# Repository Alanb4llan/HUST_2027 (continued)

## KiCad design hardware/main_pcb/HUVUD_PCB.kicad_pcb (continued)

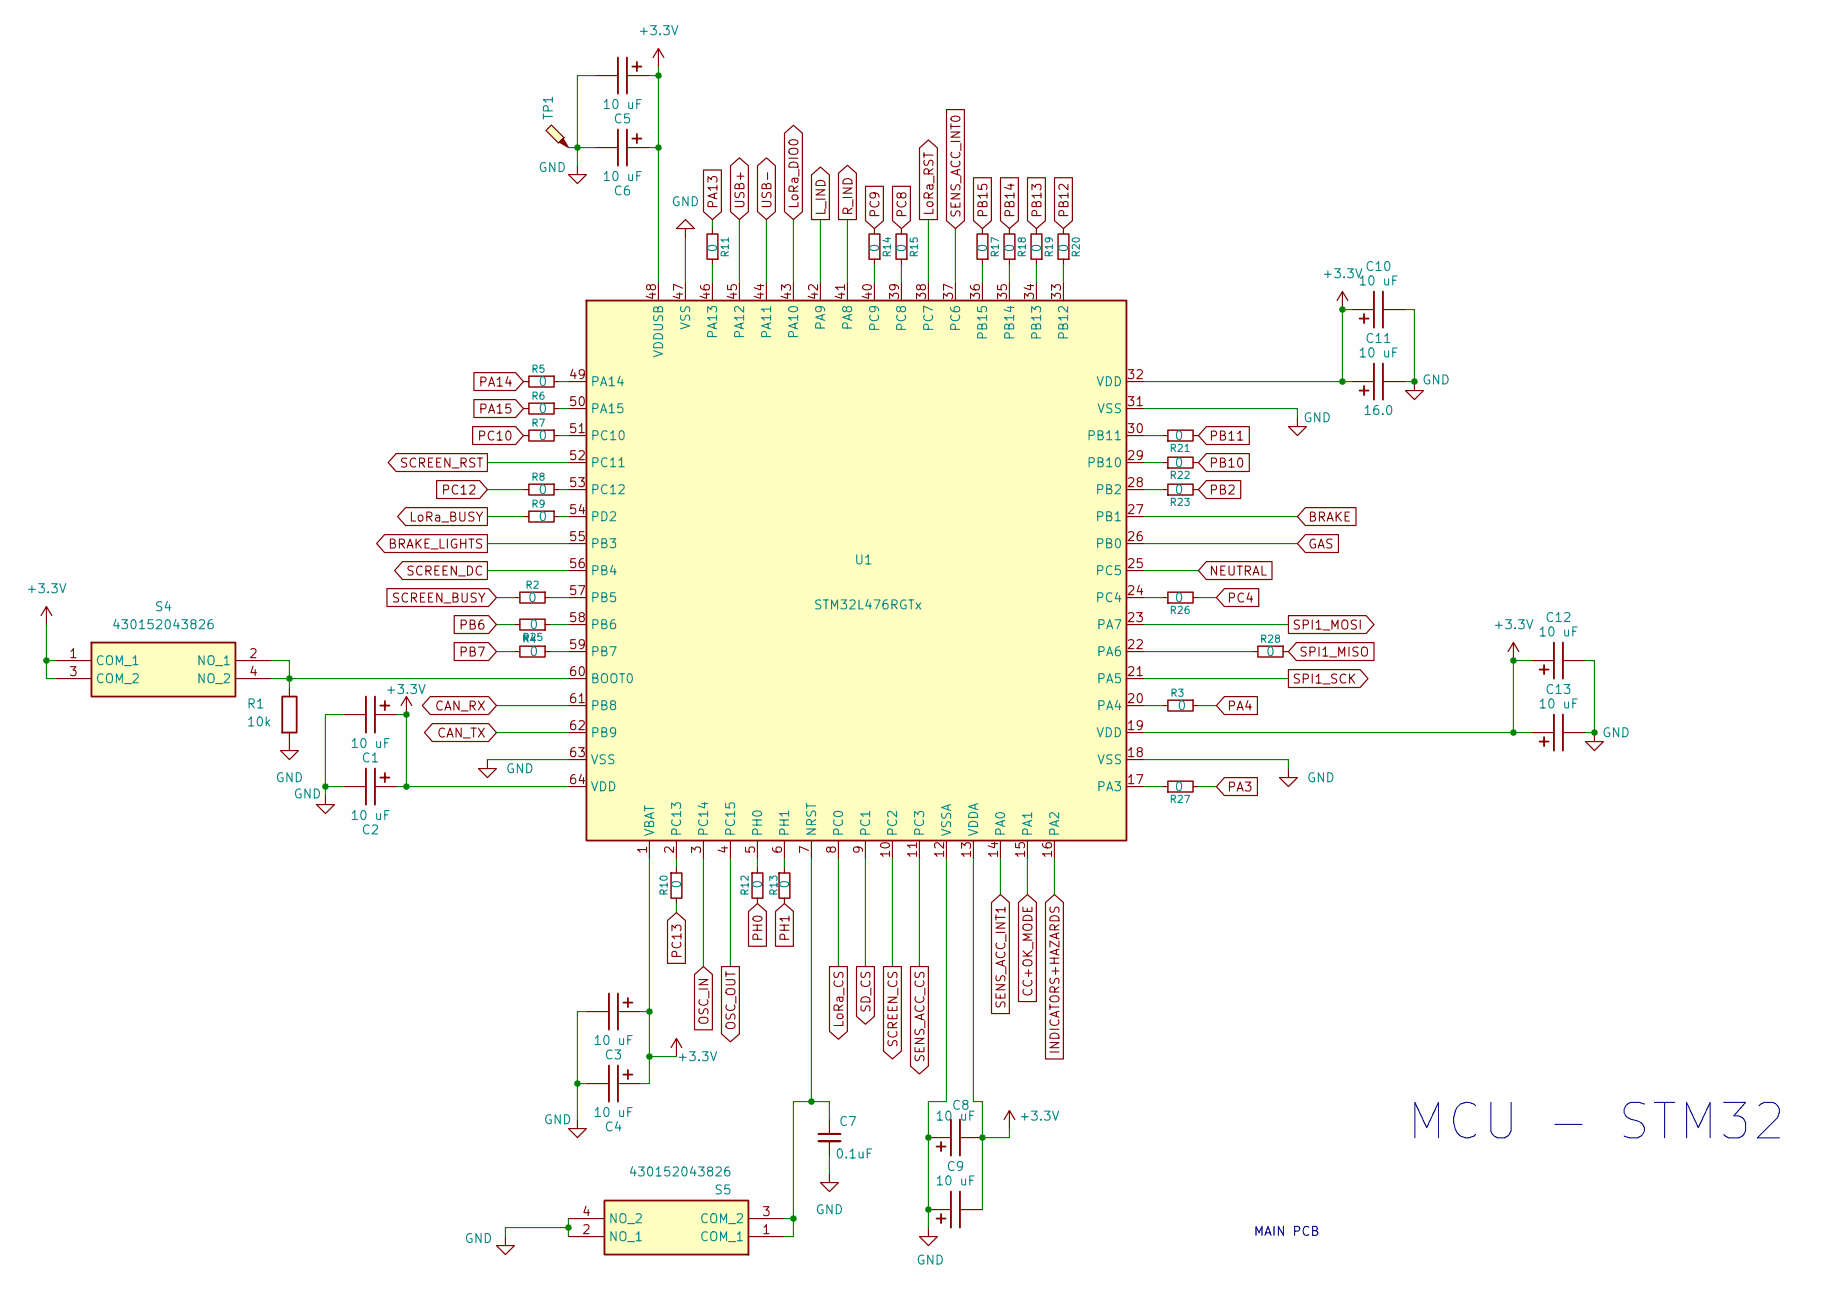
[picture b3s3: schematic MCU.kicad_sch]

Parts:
C1, C2, C3, C4, C5, C6, C8, C9, C10, C11, C12, C13: 10 uF; C_0603_1608Metric_Pad1.08x0.95mm_HandSolder; Voltage 16.0; Part Number 865080340001
C7: 0.1uF; C_0603_1608Metric_Pad1.08x0.95mm_HandSolder
R1: 10k; R_Wurth_WRIS-RSKS-0603_W
R2, R3, R4, R5, R6, R7, R8, R9, R10, R11, R12, R13, R14, R15, R17, R18, R19, R20, R21, R22, R23, R25, R26, R27, R28: 0; R_Wurth_WRIS-RSKS-0603_W
S4, S5: 430152043826; SW_Wurth_WS-TASV_430152043826; Mouser Part Number 710-430152043826
TP1: TestPoint_Probe; TestPoint_THTPad_2.0x2.0mm_Drill1.0mm
U1: STM32L476RGTx; LQFP-64_10x10mm_P0.5mm

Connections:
+3.3V: C1.1, C2.1, C3.1, C4.1, C5.1, C6.1, C8.2, C9.2, C10.1, C11.1, C12.1, C13.1, S4.1 (COM_1), S4.3 (COM_2), U1.1 (VBAT), U1.13 (VDDA), U1.19 (VDD), U1.32 (VDD), U1.48 (VDDUSB), U1.64 (VDD); also elsewhere on the board
BRAKE: U1.27 (PB1); also elsewhere on the board
BRAKE_LIGHTS: U1.55 (PB3); also elsewhere on the board
CAN_RX: U1.61 (PB8); also elsewhere on the board
CAN_TX: U1.62 (PB9); also elsewhere on the board
CC+OK_MODE: U1.15 (PA1); also elsewhere on the board
GAS: U1.26 (PB0); also elsewhere on the board
GND: C1.2, C2.2, C3.2, C4.2, C5.2, C6.2, C7.2, C8.1, C9.1, C10.2, C11.2, C12.2, C13.2, R1.2, S5.2 (NO_1), S5.4 (NO_2), TP1.1, U1.12 (VSSA), U1.18 (VSS), U1.31 (VSS), U1.47 (VSS), U1.63 (VSS); also elsewhere on the board
INDICATORS+HAZARDS: U1.16 (PA2); also elsewhere on the board
L_IND: U1.42 (PA9); also elsewhere on the board
LoRa_BUSY: R9.2; also elsewhere on the board
LoRa_CS: U1.8 (PC0); also elsewhere on the board
LoRa_DIO0: U1.43 (PA10); also elsewhere on the board
LoRa_RST: U1.38 (PC7); also elsewhere on the board
NEUTRAL: U1.25 (PC5); also elsewhere on the board
unnamed: R1.1, S4.2 (NO_1), S4.4 (NO_2), U1.60 (BOOT0)
unnamed: C7.1, S5.1 (COM_1), S5.3 (COM_2), U1.7 (NRST)
unnamed: R27.1, U1.17 (PA3)
unnamed: R3.2, U1.20 (PA4)
unnamed: R28.2, U1.22 (PA6)
unnamed: R11.1, U1.46 (PA13)
unnamed: R5.1, U1.49 (PA14)
unnamed: R6.1, U1.50 (PA15)
unnamed: R23.1, U1.28 (PB2)
unnamed: R2.1, U1.57 (PB5)
unnamed: R25.1, U1.58 (PB6)
unnamed: R4.1, U1.59 (PB7)
unnamed: R22.1, U1.29 (PB10)
unnamed: R21.1, U1.30 (PB11)
unnamed: R20.1, U1.33 (PB12)
unnamed: R19.1, U1.34 (PB13)
unnamed: R18.1, U1.35 (PB14)
unnamed: R17.1, U1.36 (PB15)
unnamed: R26.1, U1.24 (PC4)
unnamed: R15.1, U1.39 (PC8)
unnamed: R14.1, U1.40 (PC9)
unnamed: R7.1, U1.51 (PC10)
unnamed: R8.1, U1.53 (PC12)
unnamed: R10.1, U1.2 (PC13)
unnamed: R9.1, U1.54 (PD2)
unnamed: R12.1, U1.5 (PH0)
unnamed: R13.1, U1.6 (PH1)
OSC_IN: U1.3 (PC14); also elsewhere on the board
OSC_OUT: U1.4 (PC15); also elsewhere on the board
PA3: R27.2
PA4: R3.1
PA13: R11.2; also elsewhere on the board
PA14: R5.2; also elsewhere on the board
PA15: R6.2; also elsewhere on the board
PB2: R23.2; also elsewhere on the board
PB6: R25.2; also elsewhere on the board
PB7: R4.2; also elsewhere on the board
PB10: R22.2; also elsewhere on the board
PB11: R21.2; also elsewhere on the board
PB12: R20.2; also elsewhere on the board
PB13: R19.2; also elsewhere on the board
PB14: R18.2; also elsewhere on the board
PB15: R17.2; also elsewhere on the board
PC4: R26.2
PC8: R15.2; also elsewhere on the board
PC9: R14.2; also elsewhere on the board
PC10: R7.2; also elsewhere on the board
PC12: R8.2; also elsewhere on the board
PC13: R10.2; also elsewhere on the board
PH0: R12.2; also elsewhere on the board
PH1: R13.2
R_IND: U1.41 (PA8); also elsewhere on the board
SCREEN_BUSY: R2.2; also elsewhere on the board
SCREEN_CS: U1.10 (PC2); also elsewhere on the board
SCREEN_DC: U1.56 (PB4); also elsewhere on the board
SCREEN_RST: U1.52 (PC11); also elsewhere on the board
SD_CS: U1.9 (PC1); also elsewhere on the board
SENS_ACC_CS: U1.11 (PC3); also elsewhere on the board
SENS_ACC_INT0: U1.37 (PC6); also elsewhere on the board
SENS_ACC_INT1: U1.14 (PA0); also elsewhere on the board
SPI1_MISO: R28.1; also elsewhere on the board
SPI1_MOSI: U1.23 (PA7); also elsewhere on the board
SPI1_SCK: U1.21 (PA5); also elsewhere on the board
USB+: U1.45 (PA12); also elsewhere on the board
USB-: U1.44 (PA11); also elsewhere on the board

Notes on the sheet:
MCU - STM32
MAIN PCB

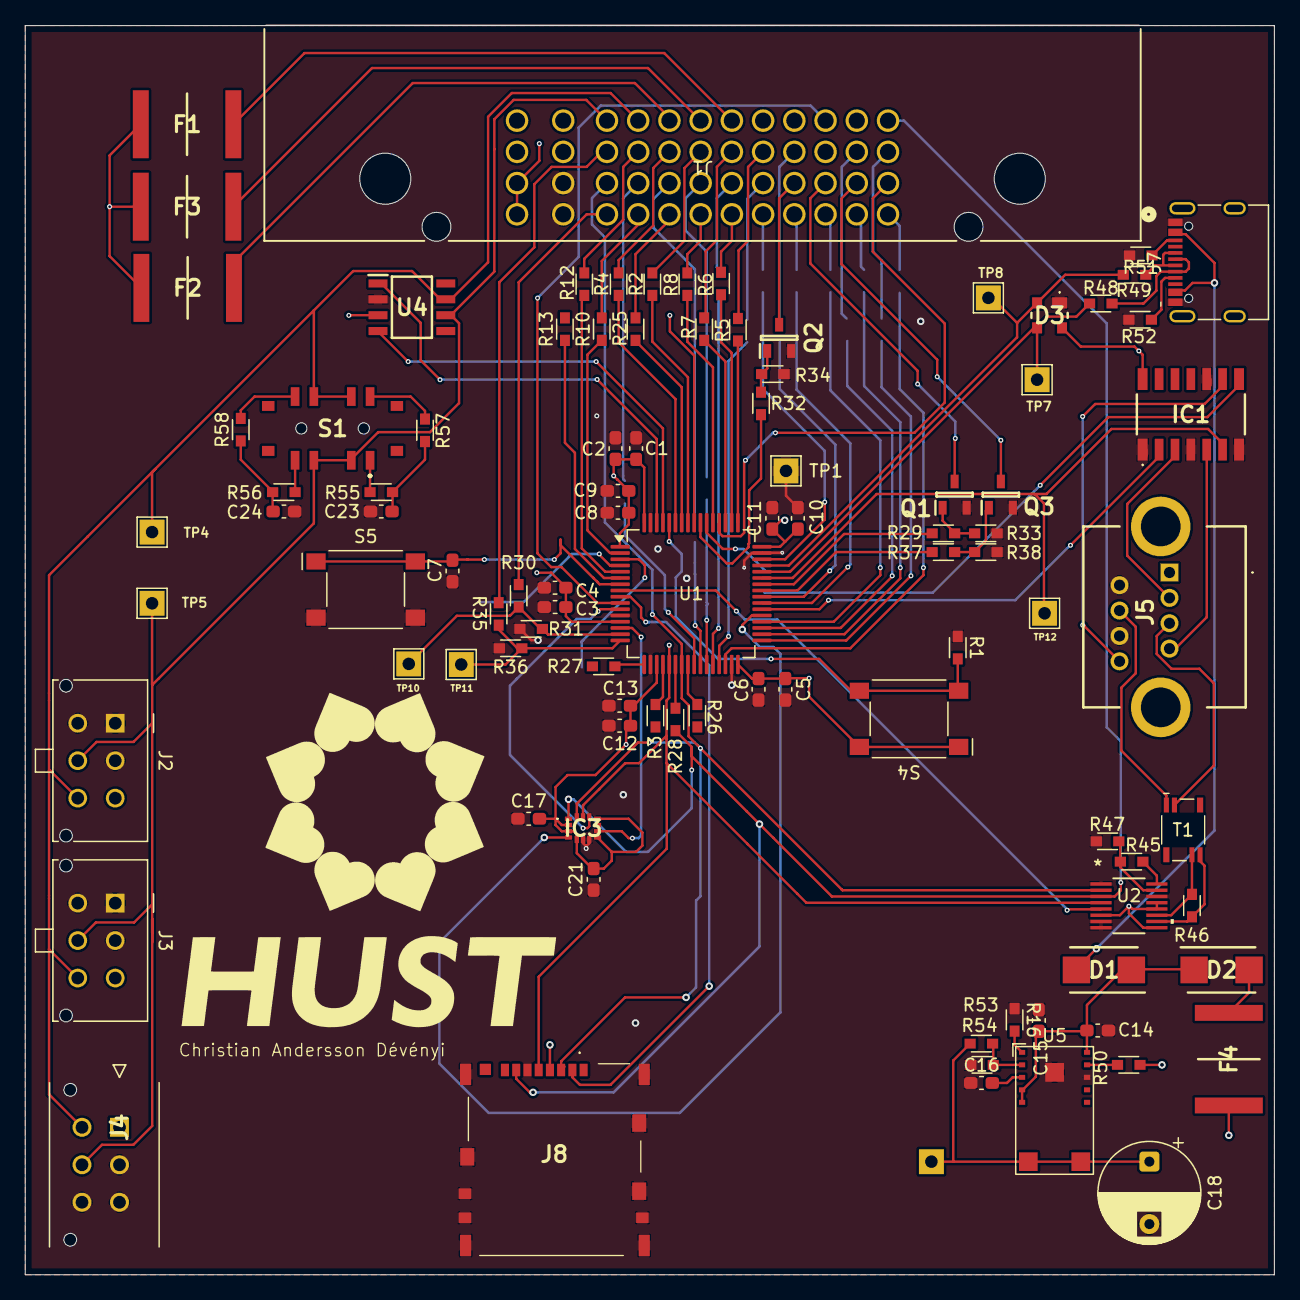
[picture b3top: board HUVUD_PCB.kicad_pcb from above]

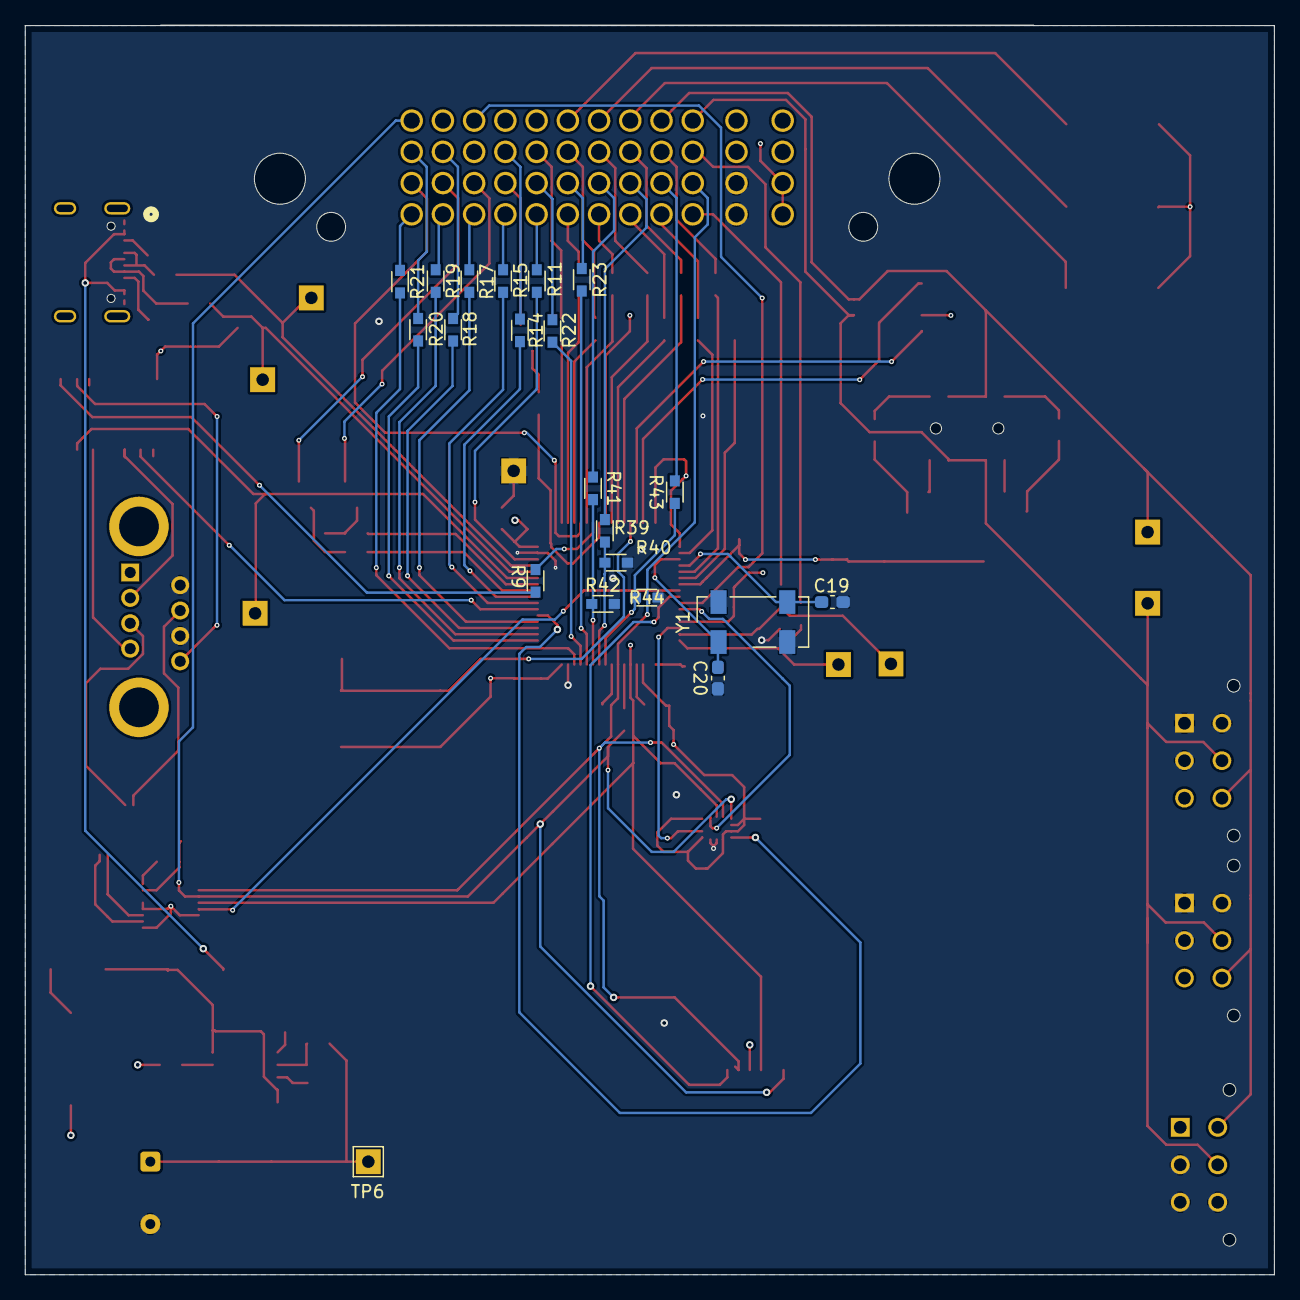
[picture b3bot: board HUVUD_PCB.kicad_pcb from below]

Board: 4 copper layers, 100.0 x 100.0 mm, 117 parts (21 on the bottom side), 120 nets.

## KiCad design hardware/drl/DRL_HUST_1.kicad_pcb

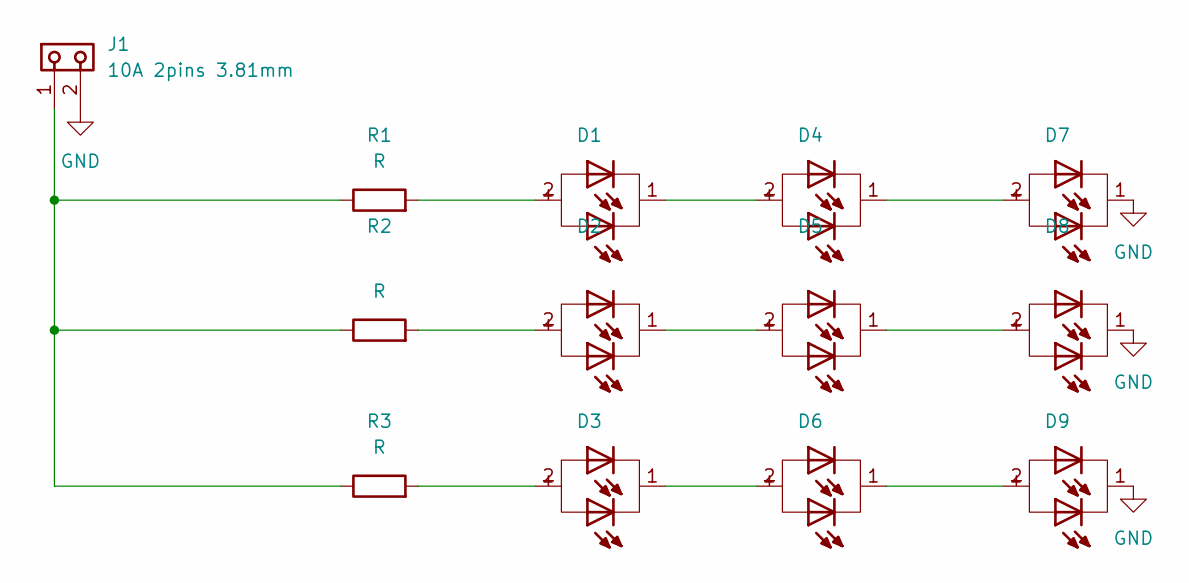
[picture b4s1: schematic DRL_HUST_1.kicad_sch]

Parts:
D1, D2, D3, D4, D5, D6, D7, D8, D9: 3030_158303250A; D_Wurth_WL-SWTP-3030; Part Number 158303250A
J1: 691409320002; J_Wurth_WR-TBL_691409320002; Part Number 691409320002
R1, R2, R3: R; R_0603_1608Metric_Pad0.98x0.95mm_HandSolder

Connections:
GND: D7.1 (-), D8.1 (-), D9.1 (-), J1.2, J1.M2
unnamed: D1.2 (+), R1.2
unnamed: D1.1 (-), D4.2 (+)
unnamed: D2.2 (+), R2.2
unnamed: D2.1 (-), D5.2 (+)
unnamed: D3.2 (+), R3.2
unnamed: D3.1 (-), D6.2 (+)
unnamed: D4.1 (-), D7.2 (+)
unnamed: D5.1 (-), D8.2 (+)
unnamed: D6.1 (-), D9.2 (+)
unnamed: J1.1, J1.M1, R1.1, R2.1, R3.1

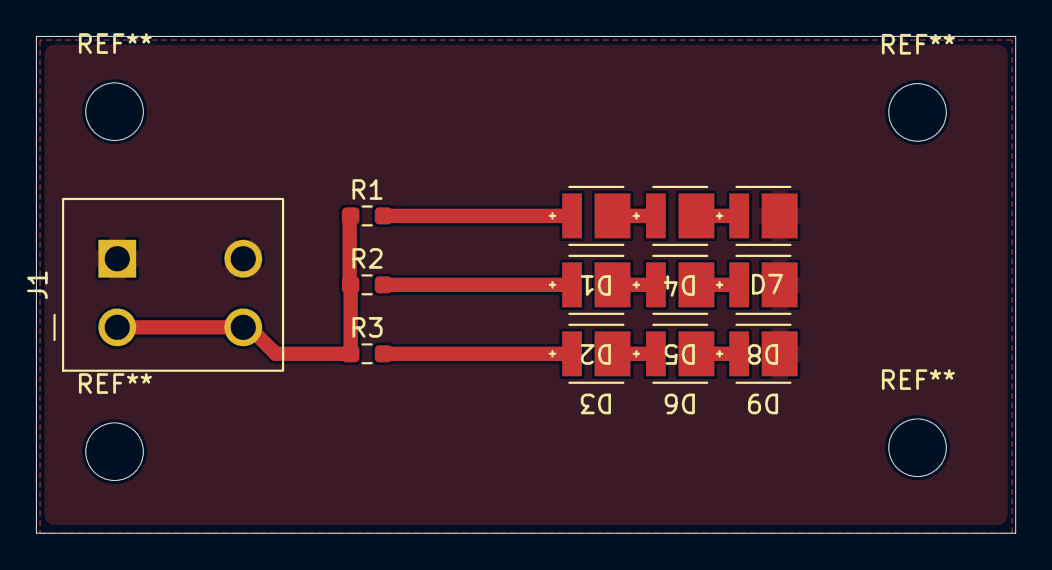
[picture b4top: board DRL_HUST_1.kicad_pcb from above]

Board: 2 copper layers, 54.4 x 27.6 mm, 13 parts (0 on the bottom side), 11 nets.

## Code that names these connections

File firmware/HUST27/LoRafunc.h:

#ifndef LORAFUNC_H
#define LORAFUNC_H

#include <LoRa.h>
#include <SPI.h>
#include <Arduino.h>
#include "global.h"

// Pins for Nucleo-L4R6G + RFM95W
// NSS=D10, SCK=D13, MISO=D12, MOSI=D11, RST=D9, DIO0=D2

#define LORA_SS   PC0   // NSS (Chip Select)
#define LORA_RST  PC7    // Reset
#define LORA_DIO0 PA10    // DIO0 (interrupt)
#define LORA_SCK  PA5
#define LORA_MISO PA6
#define LORA_MOSI PA7

// ==================================================================================
// DATA STRUCTURES FOR EFFICIENT TRANSMISSION
// ==================================================================================

// Structure 1: Critical Vehicle Data (Priority 1)
struct CriticalData {
  float velocity;          // km/h
  float packVoltage;       // V
  float packCurrent;       // A
  float motorCurrent;      // A
  uint8_t flags;           // Bit flags for errors/warnings [0]MCerror [1]BMSerror [2]HighTemp [3]Left [4]Right [5]Hazard [6]CC
  uint16_t counter;        // Packet counter 
} __attribute__((packed));

// Structure 2: Battery Data (Priority 2)
struct BatteryData {
  float lowCellVoltage;    // V
  float highCellVoltage;   // V
  float avgCellVoltage;    // V
  uint8_t cellHighTemp;    // °C
  uint8_t cellLowTemp;     // °C
  uint8_t cellAvgTemp;     // °C
  uint8_t bmsInternalTemp; // °C
  uint16_t counter;        // Packet counter
} __attribute__((packed));

// Structure 3: Motor & Thermal Data (Priority 3)
struct MotorThermalData {
  float motorTemp;         // °C
  float heatSinkTemp;      // °C
  float distance;          // km
  uint16_t counter;        // Packet counter
} __attribute__((packed));

// Structure 4: MPPT Data (Priority 4)
struct MPPTData {
  float mppt1Power;        // W
  float mppt2Power;        // W
  float mppt3Power;        // W
  float totalPower;        // W
  uint16_t counter;        // Packet counter
} __attribute__((packed));


void setupLoRa();
void sendLoRaTestMessage();  
void receiveLoRaMessage(); 
void sendConsolidatedPacket();

#endif

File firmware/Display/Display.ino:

#include <Wire.h>
#include <Adafruit_GFX.h>
#include <Adafruit_SSD1306.h>
#include <DHT.h>

#include "display.h"

// ================= SCREEN =================
#define SCREEN_WIDTH 128
#define SCREEN_HEIGHT 64

Adafruit_SSD1306 display(SCREEN_WIDTH, SCREEN_HEIGHT, &Wire, -1);

// ================= BUTTONS (CHANGE FOR YOUR BOARD) =================
// ⚠️ These are placeholders — uncomment and set correct pins for your STM32
#define BTN_HAZARD PA0
#define BTN_RIGHT  PA1
#define BTN_LEFT   PA2

// ================= DHT (OPTIONAL HARDWARE) =================
#define DHTPIN PA3
#define DHTTYPE DHT11

DHT dht(DHTPIN, DHTTYPE);

// ================= STATES =================
bool hazard = false;
bool leftActive = false;
bool rightActive = false;

bool lastHazardState = HIGH;
bool lastLeftState = HIGH;
bool lastRightState = HIGH;

bool blinkState = false;

// ================= SPEED =================
int speed = 1;

// ================= TIMERS =================
unsigned long lastBlink = 0;
unsigned long lastSpeedUpdate = 0;

// ================= SETUP =================
void setup() {

  Serial.begin(115200);

  // STM32 Wire init (default I2C pins depend on board)
  Wire.begin();

  // Buttons
  pinMode(BTN_HAZARD, INPUT_PULLUP);
  pinMode(BTN_RIGHT, INPUT_PULLUP);
  pinMode(BTN_LEFT, INPUT_PULLUP);

  // DHT (OK even if not used yet)
  dht.begin();

  // OLED init
  if (!display.begin(SSD1306_SWITCHCAPVCC, 0x3C)) {
    while (true); // stop if display fails
  }

  display.clearDisplay();
  display.display();
}

// ================= LOOP =================
void loop() {

  bool hazardBtn = digitalRead(BTN_HAZARD);
  bool rightBtn = digitalRead(BTN_RIGHT);
  bool leftBtn = digitalRead(BTN_LEFT);

  if (hazardBtn == LOW && lastHazardState == HIGH) {
    hazard = !hazard;

    if (hazard) {
      leftActive = false;
      rightActive = false;
    }
  }
  lastHazardState = hazardBtn;

  if (leftBtn == LOW && lastLeftState == HIGH) {
    leftActive = !leftActive;

    if (leftActive) {
      rightActive = false;
      hazard = false;
    }
  }
  lastLeftState = leftBtn;

  if (rightBtn == LOW && lastRightState == HIGH) {
    rightActive = !rightActive;

    if (rightActive) {
      leftActive = false;
      hazard = false;
    }
  }
  lastRightState = rightBtn;

  // ================= BLINK =================
  if (millis() - lastBlink >= 500) {
    blinkState = !blinkState;
    lastBlink = millis();
  }

  // ================= SPEED SIMULATION =================
  if (millis() - lastSpeedUpdate >= 80) {
    lastSpeedUpdate = millis();

    speed++;
    if (speed > 150) speed = 1;
  }

  drawScreen();
}

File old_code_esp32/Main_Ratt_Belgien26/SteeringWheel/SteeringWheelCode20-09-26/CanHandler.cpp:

#include "CanHandler.h"
#include "Globals.h"
#include "CruiseControl.h"
#include <ESP32-TWAI-CAN.hpp>
#include "driver/twai.h"

CanFrame msg;

void InitCAN() {
  ESP32Can.setPins(CAN_TX, CAN_RX);
  ESP32Can.setRxQueueSize(10);
  ESP32Can.setTxQueueSize(10);
  
  if (ESP32Can.begin(ESP32Can.convertSpeed(500), CAN_TX, CAN_RX, 10, 10)) {
    Serial.println("CAN bus speed 500 started!");
  }
}

void ProcessDrivingCAN() {
  if (millis() - prevmsg > 100) { 
    ProcessCruiseControl(); 
    sendDriveCAN(inputs.TargetRPM, inputs.TargetCurrent);
    sendESPCAN();
    prevmsg = millis(); 
    twai_status_info_t status; 
    twai_get_status_info(&status);
  }
  CanReadAll(); 
}

void CanReadAll() {
  if (ESP32Can.readFrame(msg, 0)) {
    switch (msg.identifier) {
      case CAN_ID_MC_ERROR:
        motor.MCerror = (msg.data[2] != 0);
        break;
      case CAN_ID_MC_BUS: 
        motor.Current = *((float*)(msg.data+4));  
        motor.Voltage = *((float*)(msg.data));    
        break;
      case CAN_ID_MC_VEL: 
        motor.VehicleVelocity = *((float*)(msg.data + 4)) * 3.6; 
        motor.RPM = *((float*)(msg.data));
        break;
      case CAN_ID_MC_TEMP: 
        motor.HeatSinkTemp = *((float*)(msg.data+4));
        motor.MotorTemp = *((float*)(msg.data));
        break;
      case CAN_ID_MC_ODO: 
        motor.Amps = *((float*)(msg.data+4)); 
        motor.Distance = *((float*)(msg.data)); 
        break;
      case CAN_ID_BMS_TEMP: 
        bms.InternalTemp = msg.data[1];
        bms.CellHighTemp = msg.data[2];
        bms.CellLowTemp = msg.data[3];
        bms.CellAverageTemp = msg.data[4];
        bms.HighTemp = (msg.data[1] >= 50 || msg.data[2] >= 50);
        break;
      case CAN_ID_BMS_PACK: {
        int16_t raw_current = (msg.data[0] << 8) | msg.data[1];
        bms.PackCurrent = raw_current / 10.0;
        
        uint16_t raw_voltage = (msg.data[2] << 8) | msg.data[3];
        bms.PackVoltage = raw_voltage / 10.0;
        
        uint16_t raw_low = (msg.data[4] << 8) | msg.data[5];
        bms.LowCellVoltage = raw_low / 10000.0;
        
        uint16_t raw_high = (msg.data[6] << 8) | msg.data[7];
        bms.HighCellVoltage = raw_high / 10000.0;
        break;
      }
      case CAN_ID_BMS_CELL:
        bms.AverageCellVoltage = ((msg.data[0] << 8) | msg.data[1]) / 10000.0;
        break;
      case CAN_ID_BMS_ERROR:
        bms.BMSerror = (msg.data[6] != 0 || msg.data[7] != 0);
        break;
      case CAN_ID_ESP_RX: 
        if(msg.data[0] != 0) { state.CCactive = false; }
        state.SafeState = (msg.data[1] != 0);
        break;
      case CAN_ID_MPPT1:
      case CAN_ID_MPPT2:
      case CAN_ID_MPPT3:
      case CAN_ID_MPPT4: {
        int mppt_idx = (msg.identifier - 0x200) / 0x10; // Maps 0x200->0, 0x210->1, etc.
        mppt[mppt_idx].InputVoltage = ((msg.data[0] << 8) | msg.data[1]) / 100.0;
        mppt[mppt_idx].InputCurrent = (int16_t)((msg.data[2] << 8) | msg.data[3]) * 0.0005;
        mppt[mppt_idx].OutputVoltage = ((msg.data[4] << 8) | msg.data[5]) / 100.0;
        mppt[mppt_idx].OutputCurrent = (int16_t)((msg.data[6] << 8) | msg.data[7]) * 0.0005;
        mppt[mppt_idx].OutputPower = mppt[mppt_idx].OutputVoltage * mppt[mppt_idx].OutputCurrent;
        break;
      }
    }
    TotMPPT = mppt[0].OutputPower + mppt[1].OutputPower + mppt[2].OutputPower + mppt[3].OutputPower;
  }
}

void sendDriveCAN(float value1, float value2) {
  uint8_t data[8]; 
  memcpy(data, &value1, sizeof(float));       
  memcpy(data + 4, &value2, sizeof(float));   
  
  twai_message_t msg1 = {0};
  msg1.identifier = CAN_ID_DRIVE_CMD;                    
  msg1.extd = 0;                               
  msg1.data_length_code = 8;                   
  memcpy(msg1.data, data, 8);
  
  ESP32Can.writeFrame(msg1);
}

void sendESPCAN() {
  uint8_t data[8] = {0};
  if (state.Left_Turn) data[0] = 1; 
  else if (state.Right_Turn) data[1] = 1; 
  else if (state.Hazard) data[2] = 1;
  
  if (inputs.Brake != 0) data[3] = 1;
  
  twai_message_t msg1 = {0};
  msg1.identifier = CAN_ID_ESP_TX; 
  msg1.extd = 0;                               
  msg1.data_length_code = 8;                   
  memcpy(msg1.data, data, 8);

  ESP32Can.writeFrame(msg1);
}
